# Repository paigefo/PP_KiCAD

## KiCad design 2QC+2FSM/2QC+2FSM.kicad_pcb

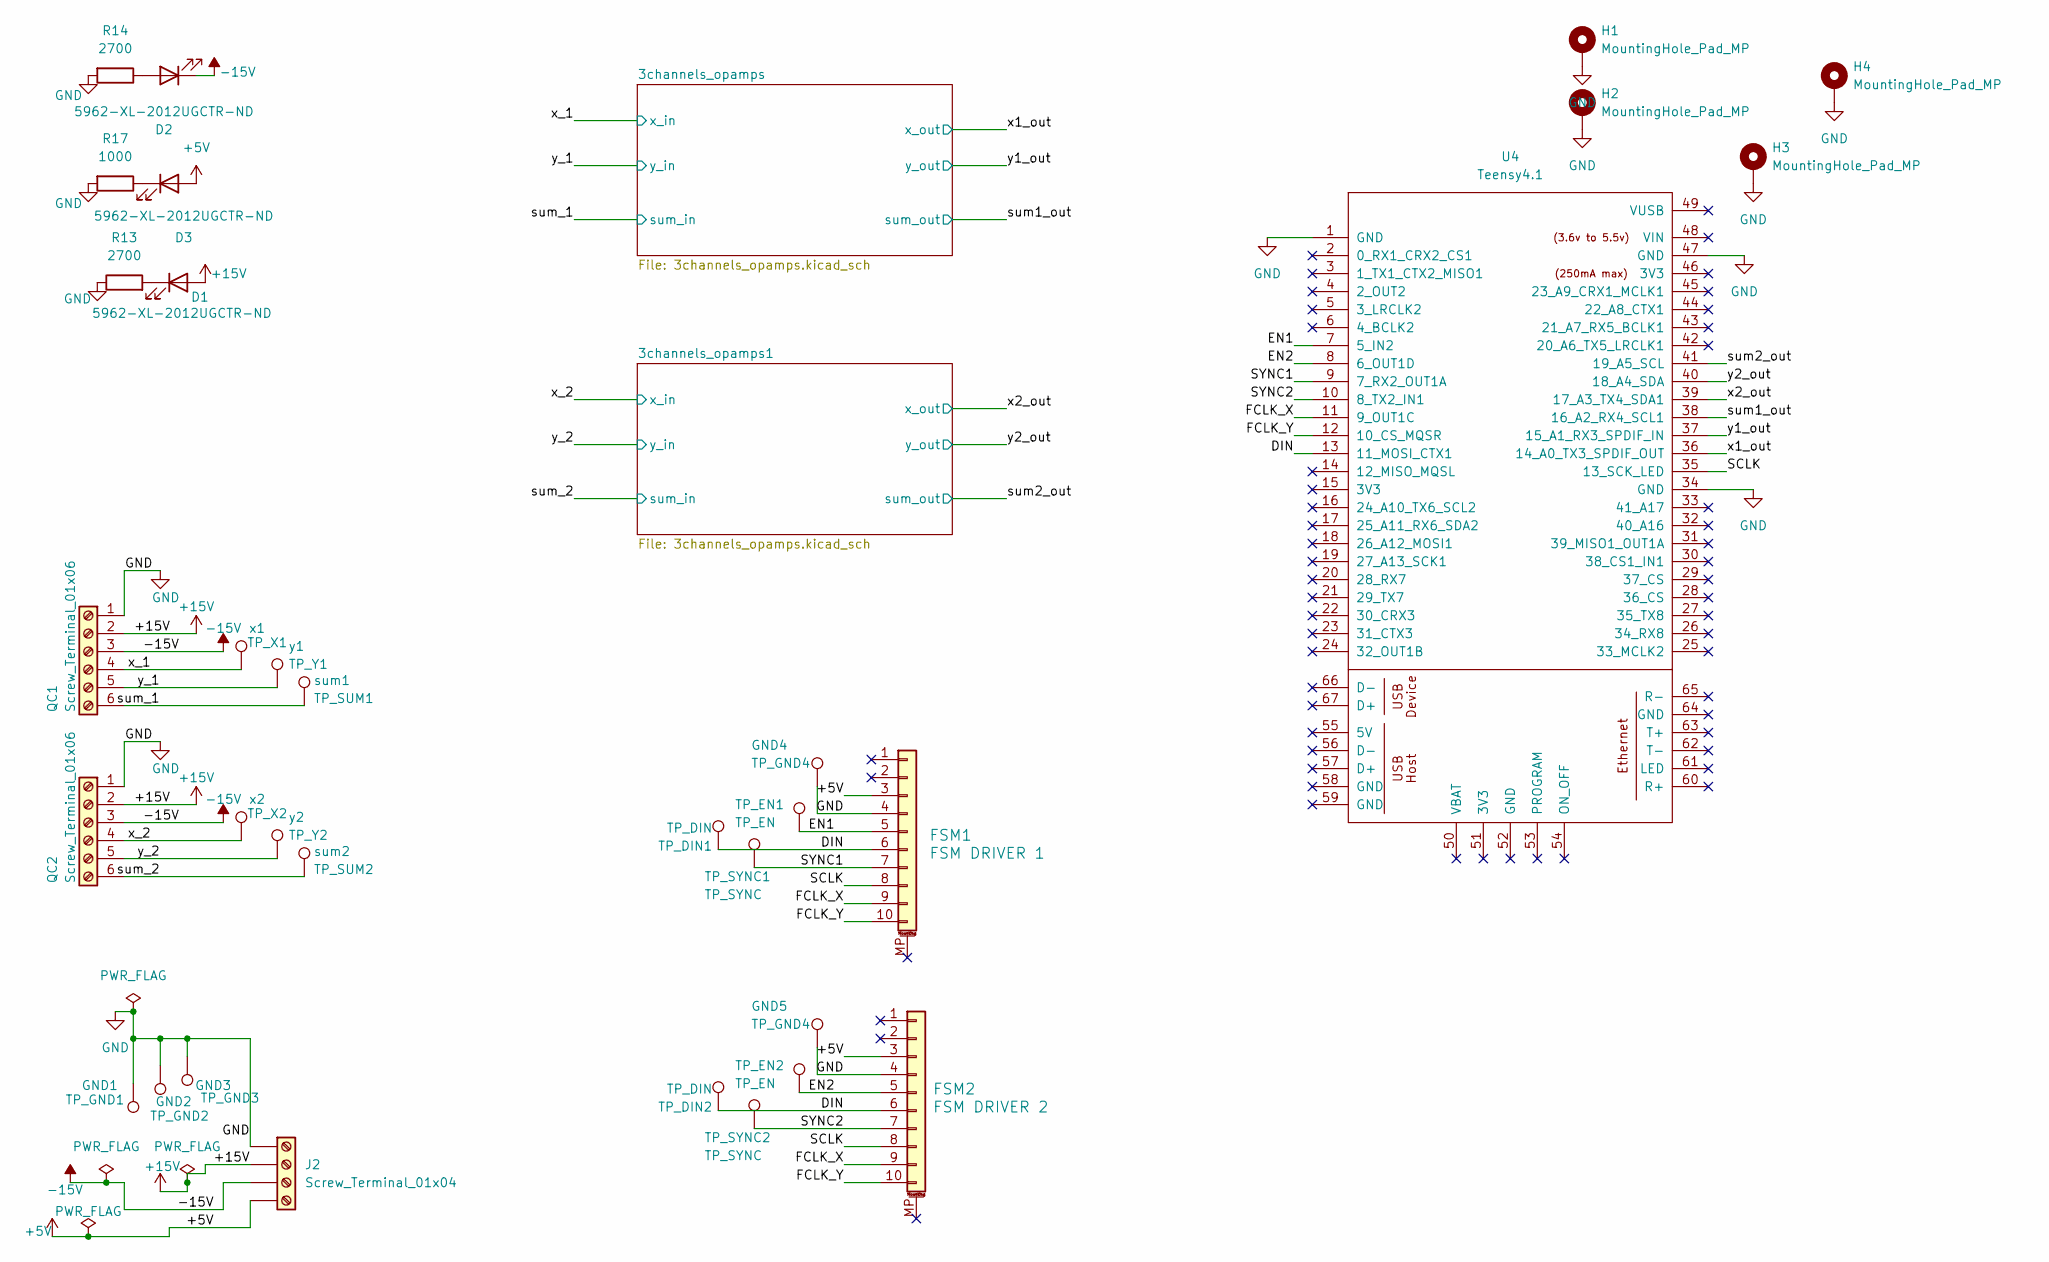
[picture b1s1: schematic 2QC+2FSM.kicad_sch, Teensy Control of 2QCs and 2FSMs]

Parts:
D1, D2, D3: 5962-XL-2012UGCTR-ND; LED_0805_2012Metric; LCSC C965815
FSM1: FSM DRIVER 1; CONN_3220-10-0100-00_CNC
FSM2: FSM DRIVER 2; CONN_3220-10-0100-00_CNC
GND1: TP_GND1; TestPoint_Loop_D2.60mm_Drill1.6mm_Beaded; LCSC C2906763
GND2: TP_GND2; TestPoint_Loop_D2.60mm_Drill1.6mm_Beaded; LCSC C2906763
GND3: TP_GND3; TestPoint_Loop_D2.60mm_Drill1.6mm_Beaded; LCSC C2906763
GND4, GND5: TP_GND4; TestPoint_Loop_D2.60mm_Drill1.6mm_Beaded; LCSC C2906763
H1, H2, H3, H4: MountingHole_Pad_MP; MountingHole_3.2mm_M3_DIN965_Pad_TopBottom
J2: Screw_Terminal_01x04; TerminalBlock_Phoenix_MKDS-1,5-4-5.08_1x04_P5.08mm_Horizont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; LCSC C5443561
QC1, QC2: Screw_Terminal_01x06; TerminalBlock_Phoenix_MKDS-1,5-6-5.08_1x06_P5.08mm_Horizont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; LCSC C2915642
R13, R14: 2700; R_0805_2012Metric; LCSC C2907305
R17: 1000; R_0805_2012Metric; LCSC C95781
TP_DIN1, TP_DIN2: TP_DIN; TestPoint_Loop_D2.60mm_Drill1.6mm_Beaded; LCSC C2906763
TP_EN1, TP_EN2: TP_EN; TestPoint_Loop_D2.60mm_Drill1.6mm_Beaded; LCSC C2906763
TP_SYNC1, TP_SYNC2: TP_SYNC; TestPoint_Loop_D2.60mm_Drill1.6mm_Beaded; LCSC C2906763
U4: Teensy4.1; Teensy41
sum1: TP_SUM1; TestPoint_Loop_D2.60mm_Drill1.6mm_Beaded; LCSC C2906763
sum2: TP_SUM2; TestPoint_Loop_D2.60mm_Drill1.6mm_Beaded; LCSC C2906763
x1: TP_X1; TestPoint_Loop_D2.60mm_Drill1.6mm_Beaded; LCSC C2906763
x2: TP_X2; TestPoint_Loop_D2.60mm_Drill1.6mm_Beaded; LCSC C2906763
y1: TP_Y1; TestPoint_Loop_D2.60mm_Drill1.6mm_Beaded; LCSC C2906763
y2: TP_Y2; TestPoint_Loop_D2.60mm_Drill1.6mm_Beaded; LCSC C2906763

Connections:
+5V: D3.2 (A), FSM1.3, FSM2.3, J2.4; also elsewhere on the board
+15V: D1.2 (A), J2.2, QC1.2, QC2.2; also elsewhere on the board
-15V: D2.1 (K), J2.3, QC1.3, QC2.3; also elsewhere on the board
/DIN: FSM1.6, FSM2.6, TP_DIN1.1, TP_DIN2.1, U4.13 (11_MOSI_CTX1)
/EN1: FSM1.5, TP_EN1.1, U4.7 (5_IN2)
/EN2: FSM2.5, TP_EN2.1, U4.8 (6_OUT1D)
/FCLK_X: FSM1.9, FSM2.9, U4.11 (9_OUT1C)
/FCLK_Y: FSM1.10, FSM2.10, U4.12 (10_CS_MQSR)
/SCLK: FSM1.8, FSM2.8, U4.35 (13_SCK_LED)
/SYNC1: FSM1.7, TP_SYNC1.1, U4.9 (7_RX2_OUT1A)
/SYNC2: FSM2.7, TP_SYNC2.1, U4.10 (8_TX2_IN1)
/sum1_out: U4.38 (16_A2_RX4_SCL1); also elsewhere on the board
/sum2_out: U4.41 (19_A5_SCL); also elsewhere on the board
/sum_1: QC1.6, sum1.1; also elsewhere on the board
/sum_2: QC2.6, sum2.1; also elsewhere on the board
/x1_out: U4.36 (14_A0_TX3_SPDIF_OUT); also elsewhere on the board
/x2_out: U4.39 (17_A3_TX4_SDA1); also elsewhere on the board
/x_1: QC1.4, x1.1; also elsewhere on the board
/x_2: QC2.4, x2.1; also elsewhere on the board
/y1_out: U4.37 (15_A1_RX3_SPDIF_IN); also elsewhere on the board
/y2_out: U4.40 (18_A4_SDA); also elsewhere on the board
/y_1: QC1.5, y1.1; also elsewhere on the board
/y_2: QC2.5, y2.1; also elsewhere on the board
GND: FSM1.4, FSM2.4, GND1.1, GND2.1, GND3.1, GND4.1, GND5.1, H1.MP, H2.MP, H3.MP, H4.MP, J2.1, QC1.1, QC2.1, R13.1, R14.2, R17.2, U4.1 (GND), U4.34 (GND), U4.47 (GND); also elsewhere on the board
unnamed: D1.1 (K), R13.2
unnamed: D2.2 (A), R14.1
unnamed: D3.1 (K), R17.1

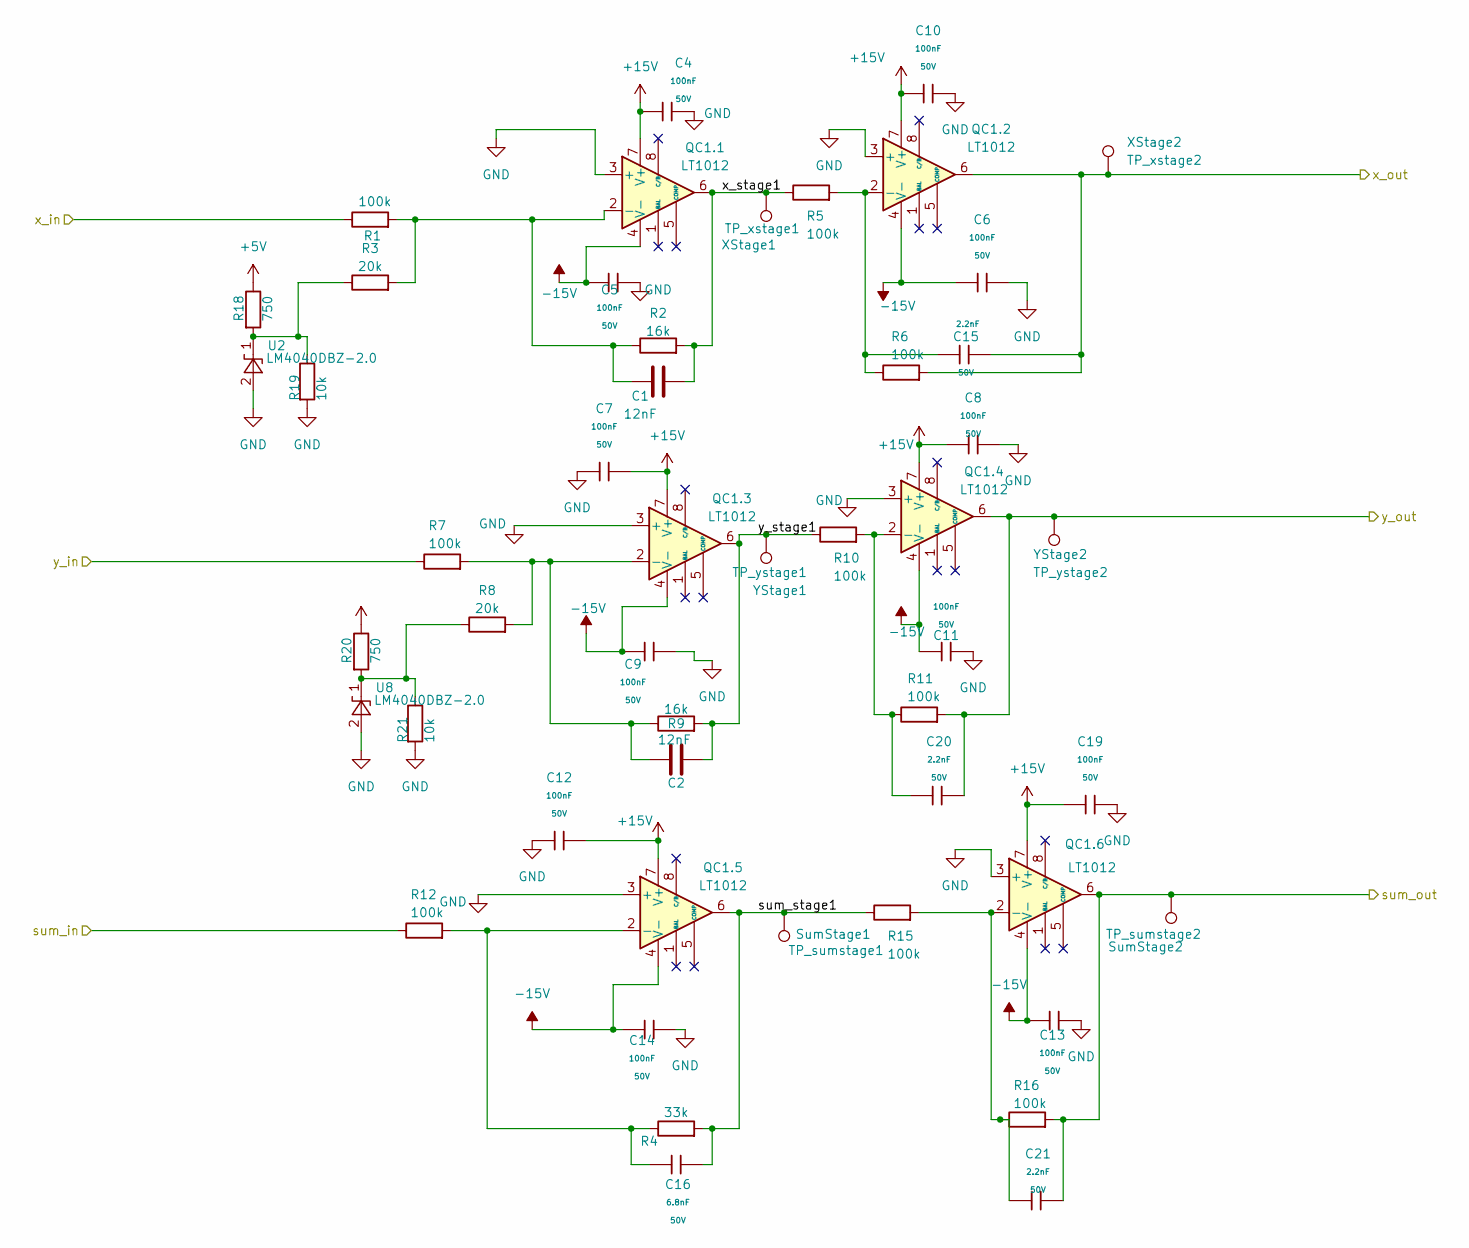
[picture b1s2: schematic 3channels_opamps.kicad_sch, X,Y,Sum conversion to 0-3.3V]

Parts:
C1, C2: 12nF; C_0603_1608Metric; LCSC C107074
C4, C5, C6, C7, C8, C9, C10, C11, C12, C13, C14, C19: 100nF; C_0603; Voltage Rated 50V; Tolerance ±10%; Part CC0603KRX7R9BB104; LCSC C14663
C15, C20, C21: 2.2nF; C_0603; Voltage Rated 50V; Tolerance ±10%; Part 0603B222K500NT; LCSC C1604
C16: 6.8nF; C_0603; Voltage Rated 50V; Tolerance ±10%; Part 0603B682K500NT; LCSC C1631
QC1.1, QC1.2, QC1.3, QC1.4, QC1.5, QC1.6: LT1012; CONN8_1-2199298-2_TEC; LCSC C305904
R1, R5, R6, R7, R10, R11, R12, R15, R16: 100k; R_0603_1608Metric; LCSC C14675
R2, R9: 16k; R_0603_1608Metric; LCSC C2907107
R3, R8: 20k; R_0603_1608Metric; LCSC C2907011
R4: 33k; R_0603_1608Metric; LCSC C2907028
R18, R20: 750; C_0603_1608Metric; LCSC C2907066
R19, R21: 10k; C_0603_1608Metric; LCSC C2930027
SumStage1: TP_sumstage1; TestPoint_Loop_D2.60mm_Drill1.6mm_Beaded; LCSC C2906763
SumStage2: TP_sumstage2; TestPoint_Loop_D2.60mm_Drill1.6mm_Beaded; LCSC C2906763
U2, U8: LM4040DBZ-2.0; SOT-23; LCSC C431732
XStage1: TP_xstage1; TestPoint_Loop_D2.60mm_Drill1.6mm_Beaded; LCSC C2906763
XStage2: TP_xstage2; TestPoint_Loop_D2.60mm_Drill1.6mm_Beaded; LCSC C2906763
YStage1: TP_ystage1; TestPoint_Loop_D2.60mm_Drill1.6mm_Beaded; LCSC C2906763
YStage2: TP_ystage2; TestPoint_Loop_D2.60mm_Drill1.6mm_Beaded; LCSC C2906763

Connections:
+5V: R18.1, R20.1; also elsewhere on the board
+15V: C4.1, C7.2, C8.1, C10.1, C12.2, C19.1, QC1.1.7 (V+), QC1.2.7 (V+), QC1.3.7 (V+), QC1.4.7 (V+), QC1.5.7 (V+), QC1.6.7 (V+); also elsewhere on the board
-15V: C5.1, C6.1, C9.1, C11.1, C13.1, C14.1, QC1.1.4 (V-), QC1.2.4 (V-), QC1.3.4 (V-), QC1.4.4 (V-), QC1.5.4 (V-), QC1.6.4 (V-); also elsewhere on the board
/3channels_opamps/sum_stage1: C16.2, QC1.5.6, R4.2, R15.1, SumStage1.1
/3channels_opamps/x_stage1: C1.2, QC1.1.6, R2.2, R5.1, XStage1.1
/3channels_opamps/y_stage1: C2.1, QC1.3.6, R9.2, R10.1, YStage1.1
/sum1_out: C21.2, QC1.6.6, R16.2, SumStage2.1; also elsewhere on the board
/sum_1: R12.1; also elsewhere on the board
/x1_out: C15.2, QC1.2.6, R6.2, XStage2.1; also elsewhere on the board
/x_1: R1.1; also elsewhere on the board
/y1_out: C20.2, QC1.4.6, R11.2, YStage2.1; also elsewhere on the board
/y_1: R7.1; also elsewhere on the board
GND: C4.2, C5.2, C6.2, C7.1, C8.2, C9.2, C10.2, C11.2, C12.1, C13.2, C14.2, C19.2, QC1.1.3 (+), QC1.2.3 (+), QC1.3.3 (+), QC1.4.3 (+), QC1.5.3 (+), QC1.6.3 (+), R19.2, R21.2, U2.2 (A), U8.2 (A); also elsewhere on the board
unnamed: C1.1, QC1.1.2 (-), R1.2, R2.1, R3.2
unnamed: C15.1, QC1.2.2 (-), R5.2, R6.1
unnamed: C2.2, QC1.3.2 (-), R7.2, R8.2, R9.1
unnamed: C20.1, QC1.4.2 (-), R10.2, R11.1
unnamed: C16.1, QC1.5.2 (-), R4.1, R12.2
unnamed: C21.1, QC1.6.2 (-), R15.2, R16.1
unnamed: R3.1, R18.2, R19.1, U2.1 (K)
unnamed: R8.1, R20.2, R21.1, U8.1 (K)

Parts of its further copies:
C3, C17, C18, C22, C23, C25, C28, C30, C32, C33, C35, C36: 100nF; C_0603; Voltage Rated 50V; Tolerance ±10%; Part CC0603KRX7R9BB104; LCSC C14663
C24, C26: 12nF; C_0603_1608Metric; LCSC C107074
C27: 6.8nF; C_0603; Voltage Rated 50V; Tolerance ±10%; Part 0603B682K500NT; LCSC C1631
C29, C31, C34: 2.2nF; C_0603; Voltage Rated 50V; Tolerance ±10%; Part 0603B222K500NT; LCSC C1604
QC2.1, QC2.2, QC2.3, QC2.4, QC2.5, QC2.6: LT1012; CONN8_1-2199298-2_TEC; LCSC C305904
R22, R24: 750; C_0603_1608Metric; LCSC C2907066
R23, R27: 10k; C_0603_1608Metric; LCSC C2930027
R25, R28, R29, R34, R35, R36, R37, R38, R39: 100k; R_0603_1608Metric; LCSC C14675
R26, R30: 20k; R_0603_1608Metric; LCSC C2907011
R31, R32: 16k; R_0603_1608Metric; LCSC C2907107
R33: 33k; R_0603_1608Metric; LCSC C2907028
SumStage3: TP_sumstage1; TestPoint_Loop_D2.60mm_Drill1.6mm_Beaded; LCSC C2906763
SumStage4: TP_sumstage2; TestPoint_Loop_D2.60mm_Drill1.6mm_Beaded; LCSC C2906763
U7, U9: LM4040DBZ-2.0; SOT-23; LCSC C431732
XStage3: TP_xstage1; TestPoint_Loop_D2.60mm_Drill1.6mm_Beaded; LCSC C2906763
XStage4: TP_xstage2; TestPoint_Loop_D2.60mm_Drill1.6mm_Beaded; LCSC C2906763
YStage3: TP_ystage1; TestPoint_Loop_D2.60mm_Drill1.6mm_Beaded; LCSC C2906763
YStage4: TP_ystage2; TestPoint_Loop_D2.60mm_Drill1.6mm_Beaded; LCSC C2906763

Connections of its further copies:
+5V: R22.1, R24.1; also elsewhere on the board
+15V: C3.2, C17.2, C25.1, C28.1, C32.1, C36.1, QC2.1.7 (V+), QC2.2.7 (V+), QC2.3.7 (V+), QC2.4.7 (V+), QC2.5.7 (V+), QC2.6.7 (V+); also elsewhere on the board
-15V: C18.1, C22.1, C23.1, C30.1, C33.1, C35.1, QC2.1.4 (V-), QC2.2.4 (V-), QC2.3.4 (V-), QC2.4.4 (V-), QC2.5.4 (V-), QC2.6.4 (V-); also elsewhere on the board
/3channels_opamps1/sum_stage1: C27.2, QC2.5.6, R33.2, R36.1, SumStage3.1
/3channels_opamps1/x_stage1: C24.2, QC2.1.6, R31.2, R34.1, XStage3.1
/3channels_opamps1/y_stage1: C26.1, QC2.3.6, R32.2, R35.1, YStage3.1
/sum2_out: C34.2, QC2.6.6, R39.2, SumStage4.1; also elsewhere on the board
/sum_2: R28.1; also elsewhere on the board
/x2_out: C31.2, QC2.2.6, R37.2, XStage4.1; also elsewhere on the board
/x_2: R25.1; also elsewhere on the board
/y2_out: C29.2, QC2.4.6, R38.2, YStage4.1; also elsewhere on the board
/y_2: R29.1; also elsewhere on the board
GND: C3.1, C17.1, C18.2, C22.2, C23.2, C25.2, C28.2, C30.2, C32.2, C33.2, C35.2, C36.2, QC2.1.3 (+), QC2.2.3 (+), QC2.3.3 (+), QC2.4.3 (+), QC2.5.3 (+), QC2.6.3 (+), R23.2, R27.2, U7.2 (A), U9.2 (A); also elsewhere on the board
unnamed: C24.1, QC2.1.2 (-), R25.2, R26.2, R31.1
unnamed: C31.1, QC2.2.2 (-), R34.2, R37.1
unnamed: C26.2, QC2.3.2 (-), R29.2, R30.2, R32.1
unnamed: C29.1, QC2.4.2 (-), R35.2, R38.1
unnamed: C27.1, QC2.5.2 (-), R28.2, R33.1
unnamed: C34.1, QC2.6.2 (-), R36.2, R39.1
unnamed: R22.2, R23.1, R26.1, U7.1 (K)
unnamed: R24.2, R27.1, R30.1, U9.1 (K)

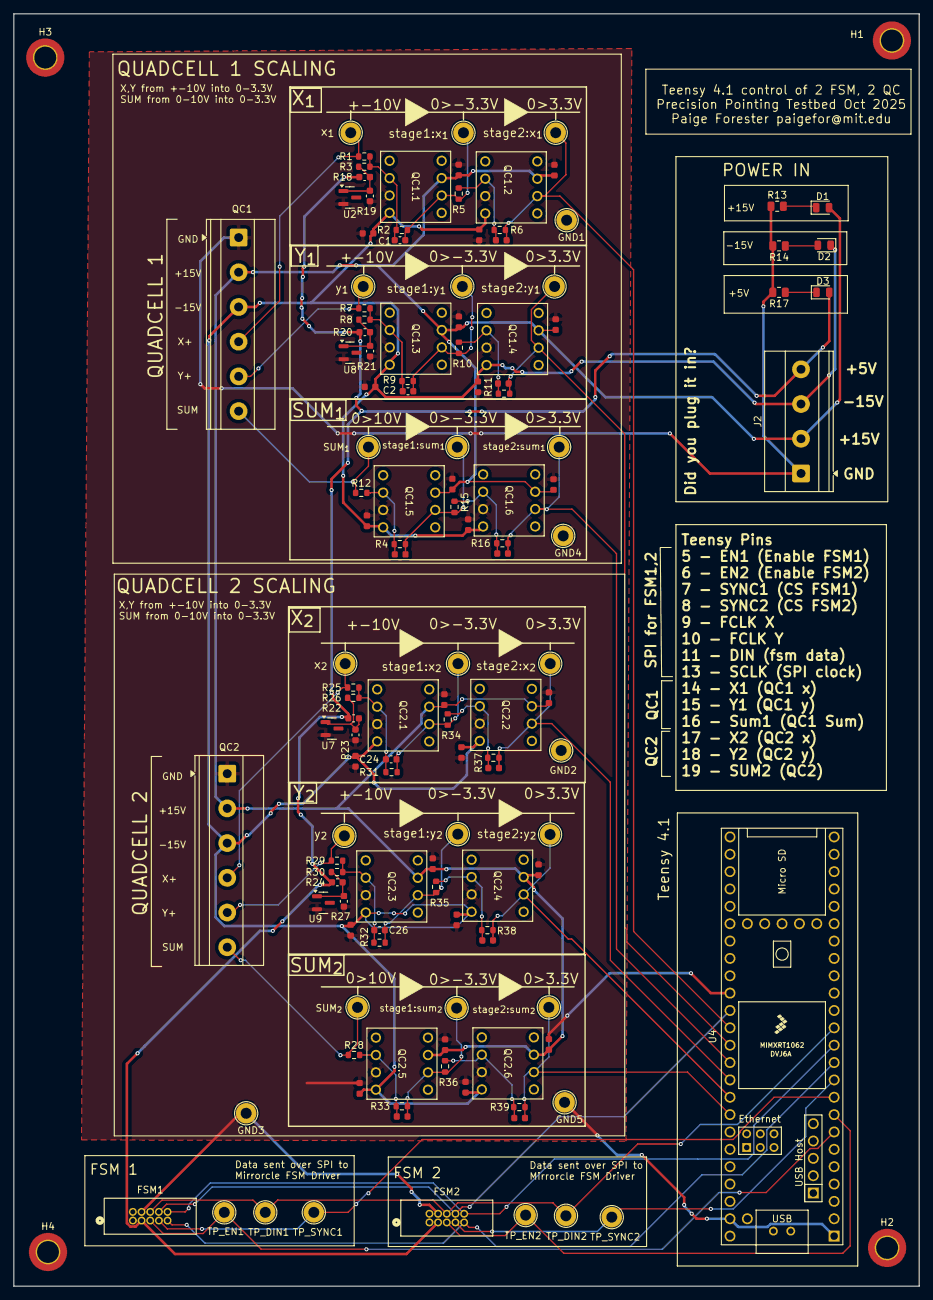
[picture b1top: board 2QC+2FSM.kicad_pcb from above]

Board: 2 copper layers, 132.5 x 186.2 mm, 133 parts (0 on the bottom side), 49 nets.

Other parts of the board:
x_{1}: TP_X1; TestPoint_Loop_D2.60mm_Drill1.6mm_Beaded

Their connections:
/x_1: x_{1}.1; also elsewhere on the board

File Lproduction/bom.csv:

Designator,Footprint,Quantity,Value,LCSC Part #
"C1, C2",0603,2,12nF,C107074
"C10, C11, C12, C13, C14, C19, C4, C5, C6, C7, C8, C9",C_0603,12,100nF,C14663
"C15, C20, C21",C_0603,3,2.2nF,C1604
C16,C_0603,1,6.8nF,C1631
"D1, D2, D3",0805,3,5962-XL-2012UGCTR-ND,C965815
GND1,TestPoint_Loop_D2.60mm_Drill1.6mm_Beaded,1,TP_GND1,C2906763
GND2,TestPoint_Loop_D2.60mm_Drill1.6mm_Beaded,1,TP_GND2,C2906763
GND3,TestPoint_Loop_D2.60mm_Drill1.6mm_Beaded,1,TP_GND3,C2906763
GND4,TestPoint_Loop_D2.60mm_Drill1.6mm_Beaded,1,TP_GND4,C2906763
J2,"TerminalBlock_Phoenix_MKDS-1,5-4-5.08_1x04_P5.08mm_Horizontal",1,Screw_Terminal_01x04,C5443561
J3,"TerminalBlock_Phoenix_MKDS-1,5-6-5.08_1x06_P5.08mm_Horizontal",1,Screw_Terminal_01x06,C2915642
J4,CONN_3220-10-0100-00_CNC,1,FSM DRIVER,C7501289 
"R1, R10, R11, R12, R15, R16, R5, R6, R7",0603,9,100k,C14675
"R13, R14",0805,2,1200,C114526
R17,0805,1,300,C17617
"R18, R20",0603,2,750,C2907066
"R19, R21",0603,2,10k,C2930027
"R2, R9",0603,2,16k,C2907107
"R3, R8",0603,2,20k,C2907011
R4,0603,1,33k,C2907028
SUMSTAGE1,TestPoint_Loop_D2.60mm_Drill1.6mm_Beaded,1,TP_sumstage1,C2906763
SUMSTAGE2,TestPoint_Loop_D2.60mm_Drill1.6mm_Beaded,1,TP_sumstage2,C2906763
TP_DIN1,TestPoint_Loop_D2.60mm_Drill1.6mm_Beaded,1,TP_DIN,C2906763
TP_EN1,TestPoint_Loop_D2.60mm_Drill1.6mm_Beaded,1,TP_EN,C2906763
TP_SYNC1,TestPoint_Loop_D2.60mm_Drill1.6mm_Beaded,1,TP_SYNC,C2906763
"U1, U10, U11, U3, U5, U6",DIP-8_W7.62mm,6,LT1012,C305904
"U2, U8",SOT-23,2,LM4040DBZ-2.0,C431732
XSTAGE1,TestPoint_Loop_D2.60mm_Drill1.6mm_Beaded,1,TP_xstage1,C2906763
XSTAGE2,TestPoint_Loop_D2.60mm_Drill1.6mm_Beaded,1,TP_xstage2,C2906763
YSTAGE1,TestPoint_Loop_D2.60mm_Drill1.6mm_Beaded,1,TP_ystage1,C2906763
YSTAGE2,TestPoint_Loop_D2.60mm_Drill1.6mm_Beaded,1,TP_ystage2,C2906763

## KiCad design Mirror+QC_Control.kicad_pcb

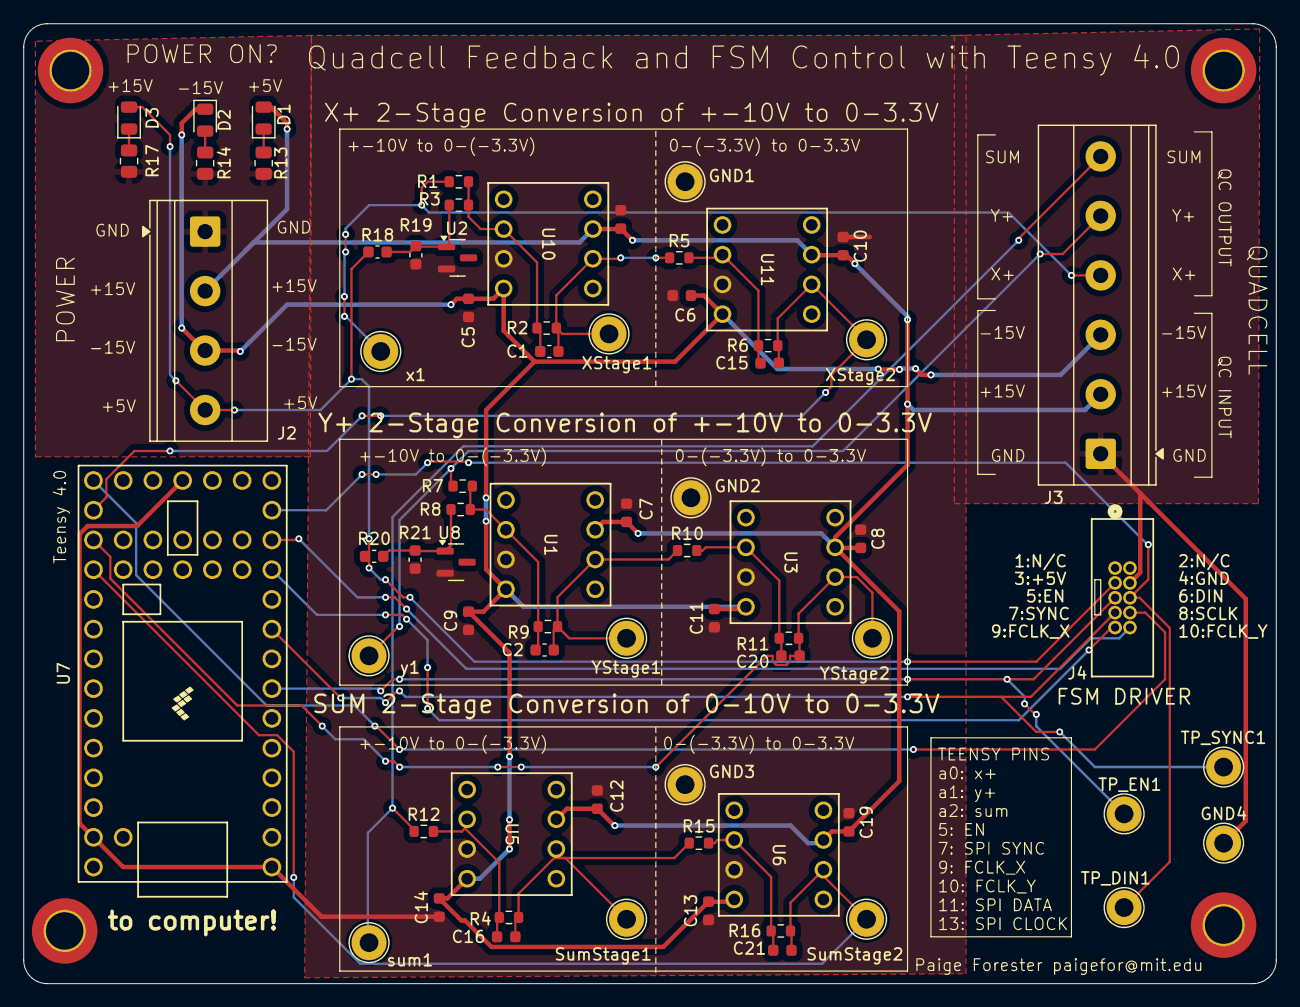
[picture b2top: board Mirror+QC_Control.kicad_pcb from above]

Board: 2 copper layers, 107.0 x 82.0 mm, 74 parts (0 on the bottom side), 30 nets.

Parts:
C1, C2: 12nF; C_0603_1608Metric
C4, C5, C6, C7, C8, C9, C10, C11, C12, C13, C14, C19: 100nF; C_0603
C15, C20, C21: 2.2nF; C_0603
C16: 6.8nF; C_0603
D1, D2, D3: 5962-XL-2012UGCTR-ND; LED_0805_2012Metric
GND1: TP_GND1; TestPoint_Loop_D2.60mm_Drill1.6mm_Beaded
GND2: TP_GND2; TestPoint_Loop_D2.60mm_Drill1.6mm_Beaded
GND3: TP_GND3; TestPoint_Loop_D2.60mm_Drill1.6mm_Beaded
GND4: TP_GND4; TestPoint_Loop_D2.60mm_Drill1.6mm_Beaded
H1, H2, H3, H4: MountingHole_Pad_MP; MountingHole_3.2mm_M3_DIN965_Pad_TopBottom
J2: Screw_Terminal_01x04; TerminalBlock_Phoenix_MKDS-1,5-4-5.08_1x04_P5.08mm_Horizont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
J3: Screw_Terminal_01x06; TerminalBlock_Phoenix_MKDS-1,5-6-5.08_1x06_P5.08mm_Horizont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
J4: FSM DRIVER; CONN_3220-10-0100-00_CNC
R1, R5, R6, R7, R10, R11, R12, R15, R16: 100k; R_0603_1608Metric
R2, R9: 16k; R_0603_1608Metric
R3, R8: 20k; R_0603_1608Metric
R4: 33k; R_0603_1608Metric
R13, R14: 1200; R_0805_2012Metric
R17: 300; R_0805_2012Metric
R18, R20: 750; C_0603_1608Metric
R19, R21: 10k; C_0603_1608Metric
SumStage1: TP_sumstage1; TestPoint_Loop_D2.60mm_Drill1.6mm_Beaded
SumStage2: TP_sumstage2; TestPoint_Loop_D2.60mm_Drill1.6mm_Beaded
TP_DIN1: TP_DIN; TestPoint_Loop_D2.60mm_Drill1.6mm_Beaded
TP_EN1: TP_EN; TestPoint_Loop_D2.60mm_Drill1.6mm_Beaded
TP_SYNC1: TP_SYNC; TestPoint_Loop_D2.60mm_Drill1.6mm_Beaded
U1, U3, U5, U6, U10, U11: LT1012; CONN8_1-2199298-2_TEC
U2, U8: LM4040DBZ-2.0; SOT-23
U7: Teensy4.0; Teensy40
XStage1: TP_xstage1; TestPoint_Loop_D2.60mm_Drill1.6mm_Beaded
XStage2: TP_xstage2; TestPoint_Loop_D2.60mm_Drill1.6mm_Beaded
YStage1: TP_ystage1; TestPoint_Loop_D2.60mm_Drill1.6mm_Beaded
YStage2: TP_ystage2; TestPoint_Loop_D2.60mm_Drill1.6mm_Beaded
sum1: TP_SUM; TestPoint_Loop_D2.60mm_Drill1.6mm_Beaded
x1: TP_X; TestPoint_Loop_D2.60mm_Drill1.6mm_Beaded
y1: TP_Y; TestPoint_Loop_D2.60mm_Drill1.6mm_Beaded

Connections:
+5V: D3.2 (A), J2.4, J4.3, R18.1, R20.1
+15V: C4.1, C7.2, C8.1, C10.1, C12.2, C19.1, D1.2 (A), J2.2, J3.2, U1.7 (V+), U3.7 (V+), U5.7 (V+), U6.7 (V+), U10.7 (V+), U11.7 (V+)
-15V: C5.1, C6.1, C9.1, C11.1, C13.1, C14.1, D2.1 (K), J2.3, J3.3, U1.4 (V-), U3.4 (V-), U5.4 (V-), U6.4 (V-), U10.4 (V-), U11.4 (V-)
/DIN: J4.6, TP_DIN1.1, U7.13 (11_MOSI_CTX1)
/EN: J4.5, TP_EN1.1, U7.7 (5_IN2)
/FCLK_X: J4.9, U7.11 (9_OUT1C)
/FCLK_Y: J4.10, U7.12 (10_CS_MQSR)
/SCLK: J4.8, U7.20 (13_SCK_CRX1_LED)
/SYNC: J4.7, TP_SYNC1.1, U7.9 (7_RX2_OUT1A)
/sum: J3.6, R12.1, sum1.1
/sum_stage1: C16.2, R4.2, R15.1, SumStage1.1, U5.6
/sum_stage2: C21.2, R16.2, SumStage2.1, U6.6, U7.23 (16_A2_RX4_SCL1)
/x+: J3.4, R1.1, x1.1
/x_stage1: C1.2, R2.2, R5.1, U10.6, XStage1.1
/x_stage2: C15.2, R6.2, U7.21 (14_A0_TX3_SPDIF_OUT), U11.6, XStage2.1
/y+: J3.5, R7.1, y1.1
/y_stage1: C2.1, R9.2, R10.1, U1.6, YStage1.1
/y_stage2: C20.2, R11.2, U3.6, U7.22 (15_A1_RX3_SPDIF_IN), YStage2.1
GND: C4.2, C5.2, C6.2, C7.1, C8.2, C9.2, C10.2, C11.2, C12.1, C13.2, C14.2, C19.2, GND1.1, GND2.1, GND3.1, GND4.1, J2.1, J3.1, J4.4, R13.1, R14.2, R17.2, R19.2, R21.2, U1.3 (+), U2.2 (A), U3.3 (+), U5.3 (+), U6.3 (+), U7.1 (GND), U7.17 (GND), U7.32 (GND), U8.2 (A), U10.3 (+), U11.3 (+)
unnamed: D1.1 (K), R13.2
unnamed: D2.2 (A), R14.1
unnamed: D3.1 (K), R17.1
unnamed: C2.2, R7.2, R8.2, R9.1, U1.2 (-)
unnamed: R3.1, R18.2, R19.1, U2.1 (K)
unnamed: C20.1, R10.2, R11.1, U3.2 (-)
unnamed: C16.1, R4.1, R12.2, U5.2 (-)
unnamed: C21.1, R15.2, R16.1, U6.2 (-)
unnamed: R8.1, R20.2, R21.1, U8.1 (K)
unnamed: C1.1, R1.2, R2.1, R3.2, U10.2 (-)
unnamed: C15.1, R5.2, R6.1, U11.2 (-)

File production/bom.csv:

Designator,Footprint,Quantity,Value,LCSC Part #
"C1, C2",0603,2,12nF,C107074
"C10, C11, C12, C13, C14, C19, C4, C5, C6, C7, C8, C9",C_0603,12,100nF,C14663
"C15, C20, C21",C_0603,3,2.2nF,C1604
C16,C_0603,1,6.8nF,C1631
"D1, D2, D3",0805,3,5962-XL-2012UGCTR-ND,C965815
GND1,TestPoint_Loop_D2.60mm_Drill1.6mm_Beaded,1,TP_GND1,C2906763
GND2,TestPoint_Loop_D2.60mm_Drill1.6mm_Beaded,1,TP_GND2,C2906763
GND3,TestPoint_Loop_D2.60mm_Drill1.6mm_Beaded,1,TP_GND3,C2906763
GND4,TestPoint_Loop_D2.60mm_Drill1.6mm_Beaded,1,TP_GND4,C2906763
J2,"TerminalBlock_Phoenix_MKDS-1,5-4-5.08_1x04_P5.08mm_Horizontal",1,Screw_Terminal_01x04,C5443561
J3,"TerminalBlock_Phoenix_MKDS-1,5-6-5.08_1x06_P5.08mm_Horizontal",1,Screw_Terminal_01x06,C2915642
J4,CONN_3220-10-0100-00_CNC,1,FSM DRIVER,
"R1, R10, R11, R12, R15, R16, R5, R6, R7",0603,9,100k,C14675
"R13, R14",0805,2,1200,C114526
R17,0805,1,300,C17617
"R18, R20",0603,2,750,C2907066
"R19, R21",0603,2,10k,C2930027
"R2, R9",0603,2,16k,C2907107
"R3, R8",0603,2,20k,C2907011
R4,0603,1,33k,C2907028
SUM1,TestPoint_Loop_D2.60mm_Drill1.6mm_Beaded,1,TP_SUM,C2906763
SUMSTAGE1,TestPoint_Loop_D2.60mm_Drill1.6mm_Beaded,1,TP_sumstage1,C2906763
SUMSTAGE2,TestPoint_Loop_D2.60mm_Drill1.6mm_Beaded,1,TP_sumstage2,C2906763
TP_DIN1,TestPoint_Loop_D2.60mm_Drill1.6mm_Beaded,1,TP_DIN,C2906763
TP_EN1,TestPoint_Loop_D2.60mm_Drill1.6mm_Beaded,1,TP_EN,C2906763
TP_SYNC1,TestPoint_Loop_D2.60mm_Drill1.6mm_Beaded,1,TP_SYNC,C2906763
"U1, U10, U11, U3, U5, U6",CONN8_1-2199298-2_TEC,6,LT1012,C305904
"U2, U8",SOT-23,2,LM4040DBZ-2.0,C431732
X1,TestPoint_Loop_D2.60mm_Drill1.6mm_Beaded,1,TP_X,C2906763
XSTAGE1,TestPoint_Loop_D2.60mm_Drill1.6mm_Beaded,1,TP_xstage1,C2906763
XSTAGE2,TestPoint_Loop_D2.60mm_Drill1.6mm_Beaded,1,TP_xstage2,C2906763
Y1,TestPoint_Loop_D2.60mm_Drill1.6mm_Beaded,1,TP_Y,C2906763
YSTAGE1,TestPoint_Loop_D2.60mm_Drill1.6mm_Beaded,1,TP_ystage1,C2906763
YSTAGE2,TestPoint_Loop_D2.60mm_Drill1.6mm_Beaded,1,TP_ystage2,C2906763

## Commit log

2025-07-16 changes after DR1
2025-07-16 changes since DR2
2025-07-16 added LCSC values and refined silkscreen. still missing capacitor values for LPFs
2025-07-17 changes include capacitance values for LPFs
2025-07-17 final changes to board with nice layout
2025-07-17 adding all LCSC part numbers
2025-07-17 added OpAmp drop in parts and oriented properly
2025-07-17 adding dropped silkscreen text
2025-07-21 removing fake FSM connector, must solder digikey components
2025-07-22 rearranged board for enclosure compatability
2025-09-08 second file for 2QC and 2FSM
2025-10-06 board layout
2025-10-07 added text and modified layout
